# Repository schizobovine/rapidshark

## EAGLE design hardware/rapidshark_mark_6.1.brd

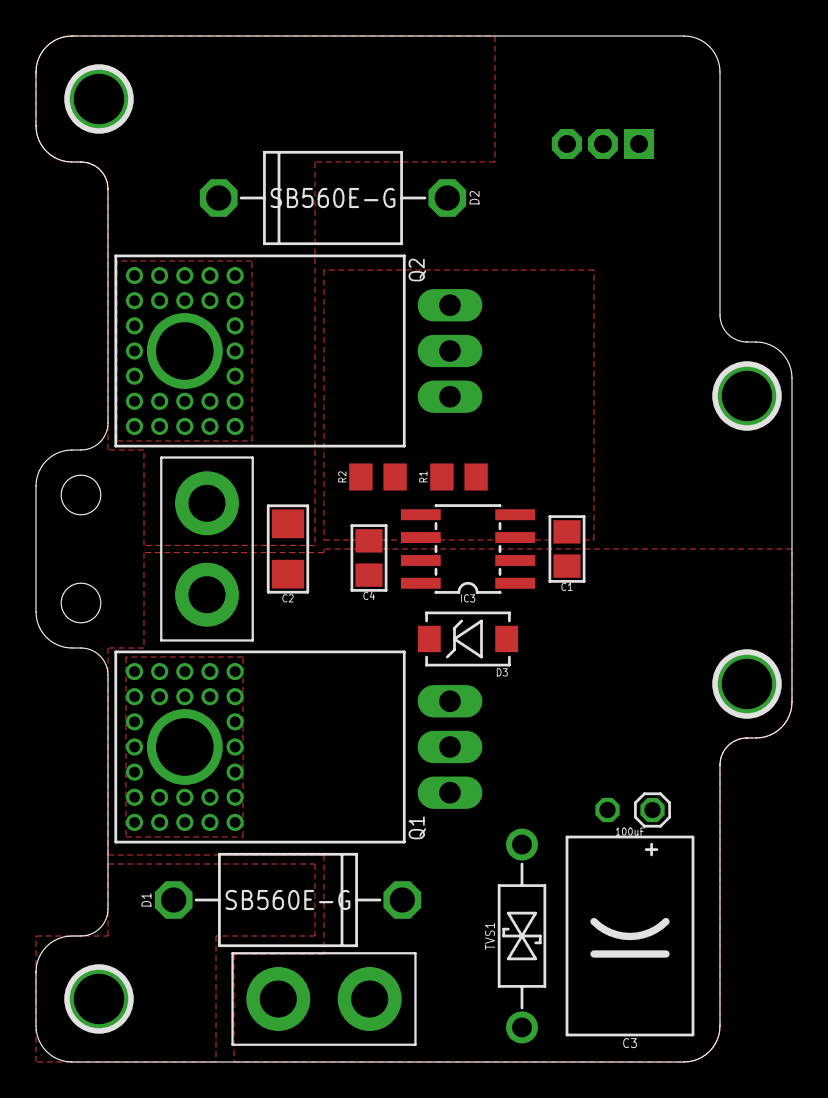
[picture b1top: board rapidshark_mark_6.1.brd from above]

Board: 2 copper layers, 42.0 x 57.0 mm, 20 parts (1 on the bottom side), 9 nets, no tracks yet.

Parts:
C1, C4: 1uF; C0805
C2: 2.2uF; C1206
C3: 100uF; E2.5-6-FLAT
D1, D2: SB560E-G; DIODE-12.70MM-FAT
D3: 1N5819; SMA-DIODE-SCHOTTKY
H1, H2, H3, H4: HOLE#2; HOLE-#2
IC3: IRS2302S; SO08
JP1: M02PTH4; 1X02_XTRA_BIG
JP2: M03JST-PTH; JST-3-PH-RA-PTH
M1: MOTORXTRA-BIG; 1X02_XTRA_BIG
Q1, Q2: FQP30N06L; TO-220-SIDE-THERM-ALT
R1, R2: 10k; R0805
TVS1: 12V; DO-41-TVS-BI-10.16MM

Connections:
INPUT: IC3.2, JP2.2
M-: C2.2, D1.A, D2.K, M1.2, Q1.3, Q2.2, Q2.GND@1, Q2.GND@2, Q2.GND@3, Q2.GND@4, Q2.GND@5, Q2.GND@6, Q2.GND@7, Q2.GND@8, Q2.GND@9, Q2.GND@10, Q2.GND@11, Q2.GND@12, Q2.GND@13, Q2.GND@14, Q2.GND@15, Q2.GND@16, Q2.GND@17, Q2.GND@18, Q2.GND@19, Q2.GND@20, Q2.GND@21, Q2.GND@22, Q2.GND@23, Q2.GND@24, Q2.GND@25, Q2.GND@26, Q2.GND@27
unnamed: IC3.7, Q1.1, R1.2
unnamed: IC3.5, Q2.1, R2.1
unnamed: C4.1, D3.C, IC3.8
unnamed: C4.2, IC3.6
SHUTDOWN: IC3.3, JP2.3
V+: C1.1, C2.1, C3.+, D1.K, D3.A, IC3.1, JP1.2, M1.1, Q1.2, Q1.GND@1, Q1.GND@2, Q1.GND@3, Q1.GND@4, Q1.GND@5, Q1.GND@6, Q1.GND@7, Q1.GND@8, Q1.GND@9, Q1.GND@10, Q1.GND@11, Q1.GND@12, Q1.GND@13, Q1.GND@14, Q1.GND@15, Q1.GND@16, Q1.GND@17, Q1.GND@18, Q1.GND@19, Q1.GND@20, Q1.GND@21, Q1.GND@22, Q1.GND@23, Q1.GND@24, Q1.GND@25, Q1.GND@26, Q1.GND@27, TVS1.P$1
V-: C1.2, C3.-, D2.A, IC3.4, JP1.1, Q2.3, R1.1, R2.2, TVS1.P$2

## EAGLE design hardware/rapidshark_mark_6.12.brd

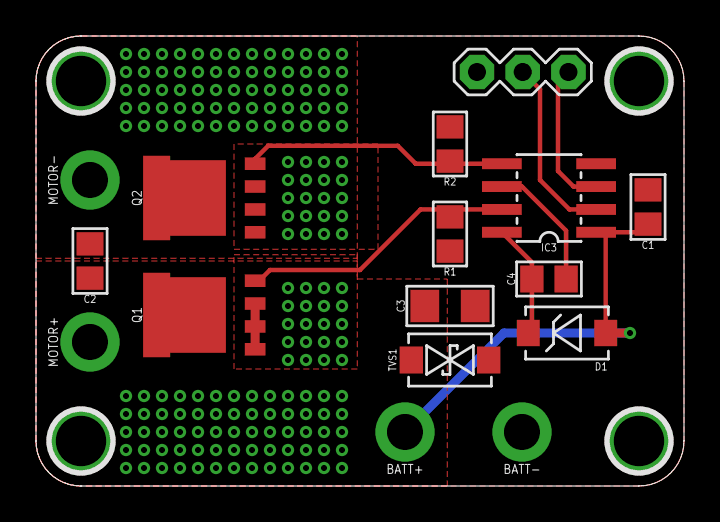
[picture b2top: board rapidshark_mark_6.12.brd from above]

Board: 2 copper layers, 36.0 x 25.0 mm, 20 parts (0 on the bottom side), 9 nets.

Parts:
BATT+: M01PTH_2MM; 1X01_2MM
BATT-: M01PTH_2MM; 1X01_2MM
C1, C4: 1uF; C0805
C2: 2.2uF; C0805
C3: 47uF; C1206
D1: SMA; SMA-DIODE-SCHOTTKY
H1, H2, H3, H4: HOLE#2; HOLE-#2
IC3: IRS2302S; SO08
JP2: M03PTH; 1X03
MOTOR+: M01PTH_2MM; 1X01_2MM
MOTOR-: M01PTH_2MM; 1X01_2MM
Q1, Q2: LFPAK56
R1, R2: 10k; R0805
TVS1: 12V; SMA-DIODE-TVS-BIDIR

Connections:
INPUT: IC3.2, JP2.2
M-: C2.2, MOTOR-.1, Q1.1, Q1.2, Q1.3, Q2.MB@1, Q2.MB@2
unnamed: IC3.7, Q1.4, R1.2
unnamed: IC3.5, Q2.4, R2.1
unnamed: C4.1, D1.C, IC3.8
unnamed: C4.2, IC3.6
SHUTDOWN: IC3.3, JP2.3
V+: BATT+.1, C1.1, C2.1, C3.1, D1.A, IC3.1, MOTOR+.1, Q1.MB@1, Q1.MB@2, TVS1.1
V-: BATT-.1, C1.2, C3.2, IC3.4, Q2.1, Q2.2, Q2.3, R1.1, R2.2, TVS1.2

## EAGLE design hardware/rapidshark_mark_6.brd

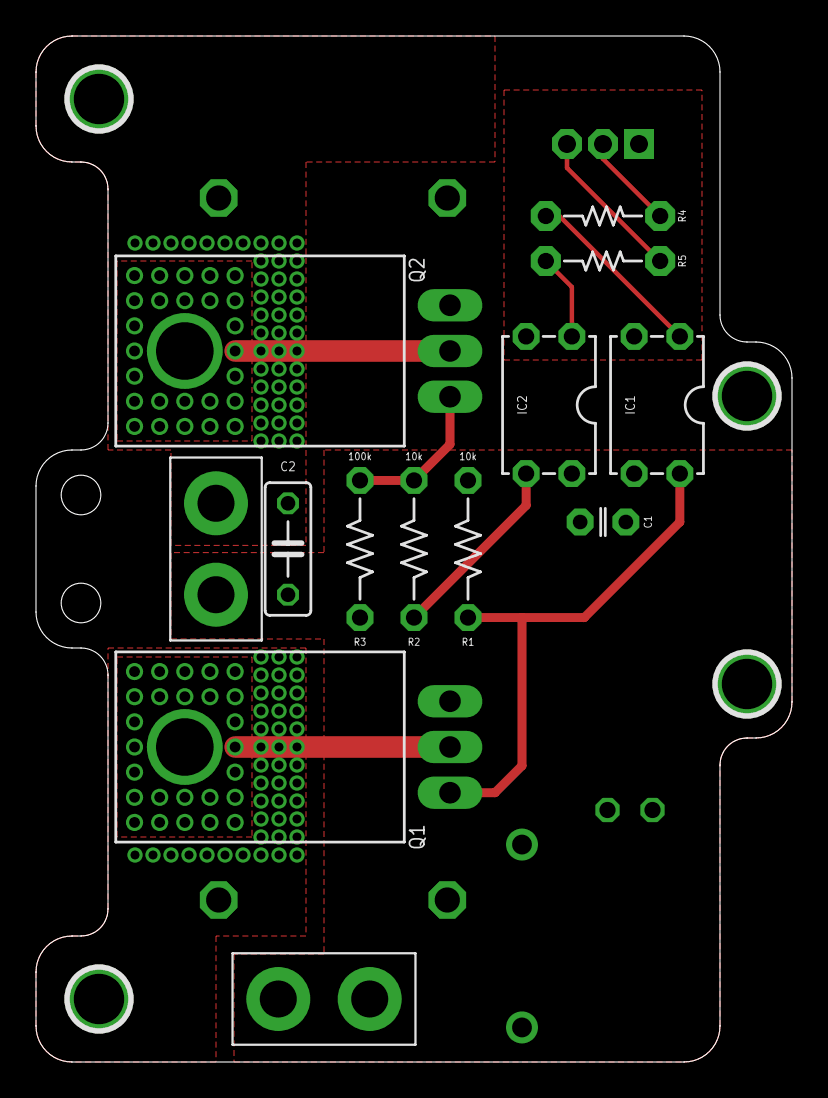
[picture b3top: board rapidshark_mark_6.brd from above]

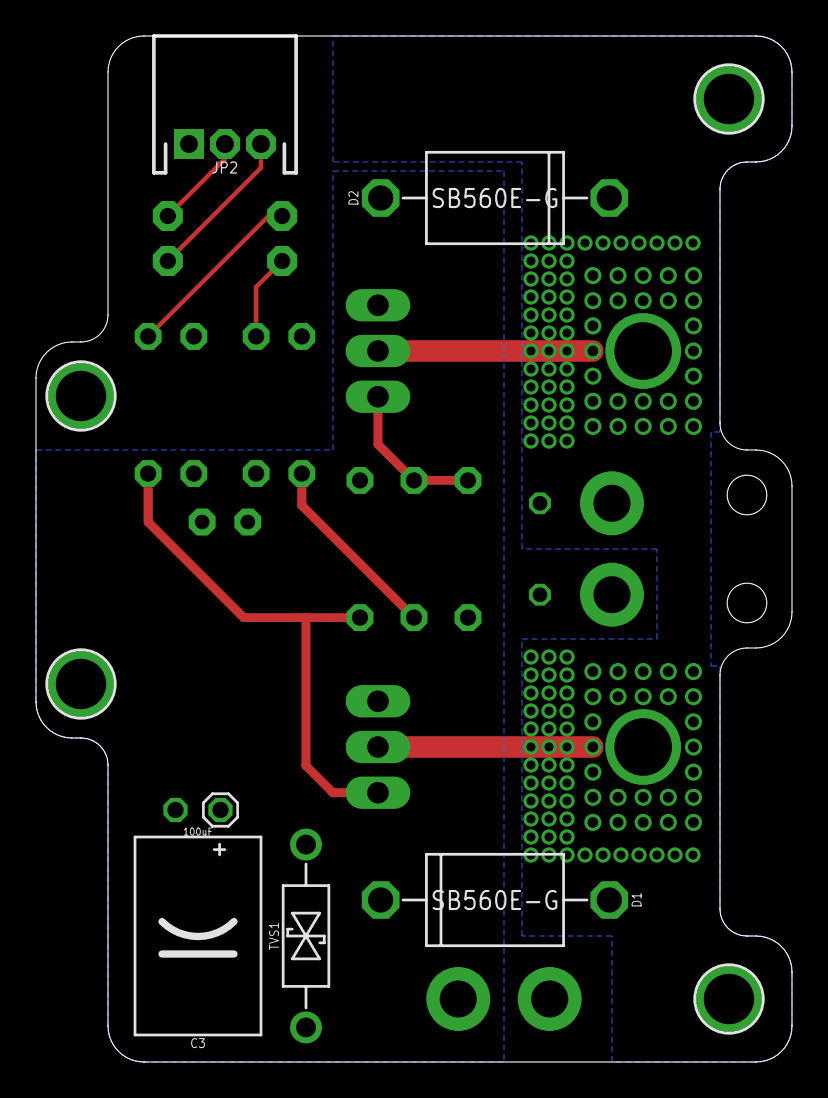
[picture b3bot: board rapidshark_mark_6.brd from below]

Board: 2 copper layers, 42.0 x 57.0 mm, 22 parts (5 on the bottom side), 11 nets.

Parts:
C1: 1uF; C025-024X044
C2: 2.2uF; C050-025X075
C3: 100uF; E2.5-6-FLAT
D1, D2: SB560E-G; DIODE-12.70MM-FAT
H1, H2, H3, H4: HOLE#2; HOLE-#2
IC1, IC2: OPTO_ISO; DIL04
JP1: M02PTH4; 1X02_XTRA_BIG
JP2: M03JST-PTH; JST-3-PH-RA-PTH
M1: MOTORXTRA-BIG; 1X02_XTRA_BIG
Q1: FQP27P06; TO-220-SIDE-THERM-ALT
Q2: FQP30N06L; TO-220-SIDE-THERM-ALT
R1, R2: 10k; RESISTOR-AXIAL-PTH-7.62MM
R3: 100k; RESISTOR-AXIAL-PTH-7.62MM
R4, R5: 220R; RESISTOR-AXIAL-PTH-6.35MM
TVS1: 12V; DO-41-TVS-BI-10.16MM

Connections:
CTRL_HIGH: JP2.2, R4.P$1
CTRL_LOW: JP2.3, R5.P$1
GND: IC1.2, IC2.2, JP2.1
M-: C2.2, D1.A, D2.K, M1.2, Q1.2, Q1.GND@1, Q1.GND@2, Q1.GND@3, Q1.GND@4, Q1.GND@5, Q1.GND@6, Q1.GND@7, Q1.GND@8, Q1.GND@9, Q1.GND@10, Q1.GND@11, Q1.GND@12, Q1.GND@13, Q1.GND@14, Q1.GND@15, Q1.GND@16, Q1.GND@17, Q1.GND@18, Q1.GND@19, Q1.GND@20, Q1.GND@21, Q1.GND@22, Q1.GND@23, Q1.GND@24, Q1.GND@25, Q1.GND@26, Q1.GND@27, Q2.2, Q2.GND@1, Q2.GND@2, Q2.GND@3, Q2.GND@4, Q2.GND@5, Q2.GND@6, Q2.GND@7, Q2.GND@8, Q2.GND@9, Q2.GND@10, Q2.GND@11, Q2.GND@12, Q2.GND@13, Q2.GND@14, Q2.GND@15, Q2.GND@16, Q2.GND@17, Q2.GND@18, Q2.GND@19, Q2.GND@20, Q2.GND@21, Q2.GND@22, Q2.GND@23, Q2.GND@24, Q2.GND@25, Q2.GND@26, Q2.GND@27
unnamed: IC1.4, Q1.1, R1.P$1
unnamed: Q2.1, R2.P$2, R3.P$2
unnamed: IC1.1, R4.P$2
unnamed: IC2.1, R5.P$2
unnamed: IC2.3, R2.P$1
V+: C1.1, C2.1, C3.+, D1.K, IC2.4, JP1.2, M1.1, Q1.3, R1.P$2, TVS1.P$1
V-: C1.2, C3.-, D2.A, IC1.3, JP1.1, Q2.3, R3.P$1, TVS1.P$2

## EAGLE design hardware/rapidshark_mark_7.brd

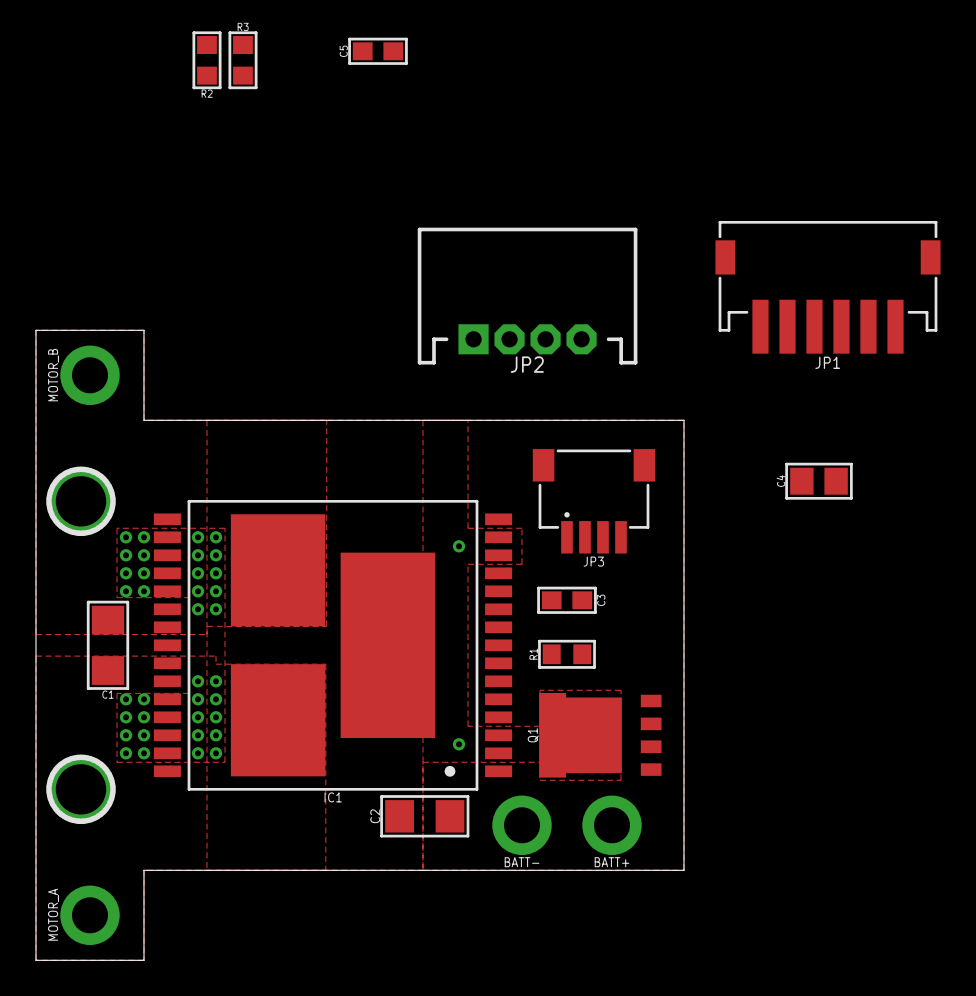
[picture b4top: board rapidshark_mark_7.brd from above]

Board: 2 copper layers, 36.0 x 35.0 mm, 19 parts (0 on the bottom side), 11 nets, no tracks yet.

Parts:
BATT+: M01PTH_2MM; 1X01_2MM
BATT-: M01PTH_2MM; 1X01_2MM
C1: 2.2uF; C1206
C2: 47uF; C3216
C3, C5: 0.1uF; C0603
C4: 0.1uF; C0805
H1, H2: HOLE#2; HOLE-#2
IC1: VNH5019A
JP1: M06JST-ZH-SMD-RA; JST-6-ZH-RA-SMD
JP2: M04JST-PTH; JST-4-PH-RA-PTH
JP3: M04JST-SH-SMD-RA; 1X04-JST-SH-1MM-SMT-RA
MOTOR_A: M01PTH_2MM; 1X01_2MM
MOTOR_B: M01PTH_2MM; 1X01_2MM
Q1: PSMN4R0-30YLD; LFPAK56
R1, R2, R3: 10k; R0603

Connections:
EN_A: IC1.5, R1.1
EN_B: IC1.9, R2.1
GND: C5.2, JP2.1, R3.1
GND1: BATT-.1, C2.2, C3.2, C4.2, IC1.17, IC1.18, IC1.19, IC1.20, IC1.26, IC1.27, IC1.28, IC1.29
MOTOR_A: C1.1, IC1.1, IC1.24, IC1.25, IC1.30, IC1.HS2, MOTOR_A.1
MOTOR_B: C1.2, IC1.15, IC1.16, IC1.21, IC1.22, IC1.HS3, MOTOR_B.1
unnamed: IC1.11, Q1.4
PWM: IC1.7, R3.2
VBAT: BATT+.1, C4.1, IC1.12, Q1.1, Q1.2, Q1.3
VCC: C2.1, C3.1, IC1.2, IC1.3, IC1.13, IC1.14, IC1.23, IC1.HS1, Q1.MB@1, Q1.MB@2
VDD: C5.1, JP2.4, R1.2, R2.2

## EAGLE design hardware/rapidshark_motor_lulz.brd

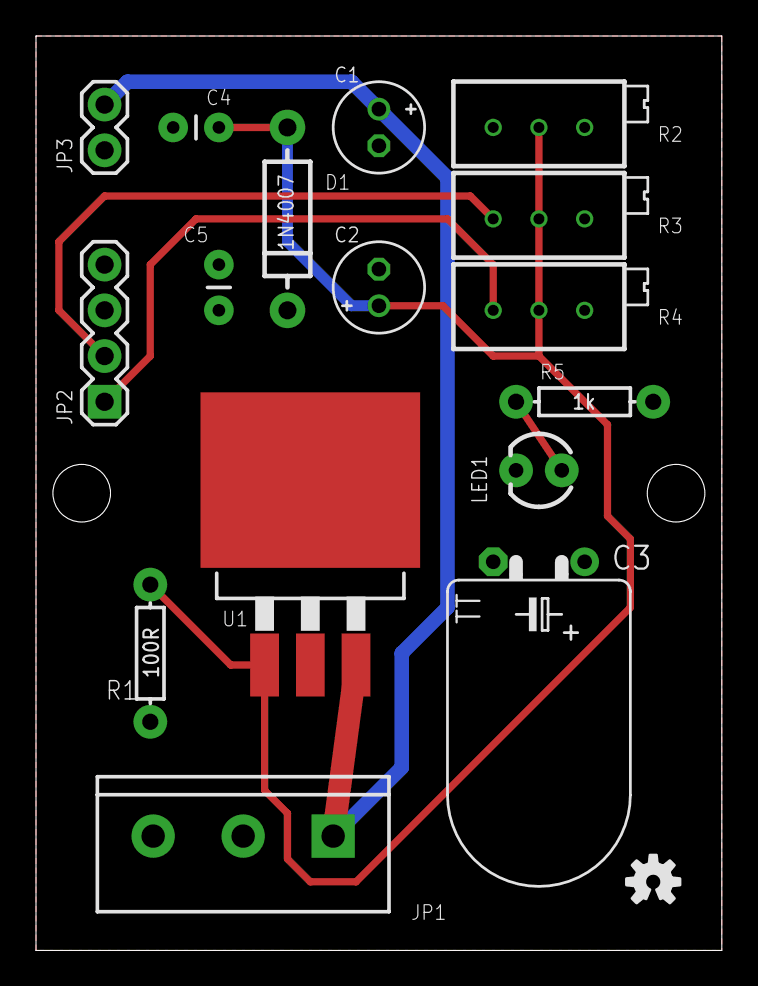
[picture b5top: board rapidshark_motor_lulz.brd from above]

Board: 2 copper layers, 38.1 x 50.8 mm, 18 parts (0 on the bottom side), 7 nets.

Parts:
C1, C2: 10uF; E2-5
C3: 150uF; TT5D11L
C4, C5: 1uF; CAP-PTH-SMALL
D1: 1N4007; DIODE-1N4001
FRAME1: FRAME-LETTER; CREATIVE_COMMONS
JP1: TRG_ASM_CON; SCREWTERMINAL-5MM-3
JP2: SPEED_SELECT; 1X04
JP3: UC_PWR_CON; 1X02
LED1: GREEN; LED3MM
LOGO1: OSHW-LOGOS; OSHW-LOGO-S
R1: 100R; AXIAL-0.3
R2, R4: 1k; RTRIMT93XA
R3: 2k; RTRIMT93XA
R5: 1k; AXIAL-0.3
U1: V_REG_LD1085D2; D2PACK/A

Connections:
ADJ: C2.+, C4.1, D1.A, R1.P$1, R2.2, R3.2, R4.2, U1.1
GND: C1.-, C2.-, C3.-, C4.2, C5.2, JP1.3, JP2.4, JP3.2, LED1.K, R2.1
unnamed: JP2.2, R3.1
unnamed: JP2.1, R4.1
unnamed: LED1.A, R5.P$1
V_BATT: C1.+, JP1.1, JP3.1, U1.3
V_OUT: C3.+, C5.1, D1.C, JP1.2, R1.P$2, R5.P$2, U1.2, U1.TAB

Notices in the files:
parts and their libraries:
SparkFun-PowerIC: Licensing: Creative Commons ShareAlike 4.0 International - https://creativecommons.org/licenses/by-sa/4.0
SparkFun-Aesthetics: Released under the Creative Commons Attribution Share-Alike 4.0 License
SparkFun-Aesthetics: https://creativecommons.org/licenses/by-sa/4.0
